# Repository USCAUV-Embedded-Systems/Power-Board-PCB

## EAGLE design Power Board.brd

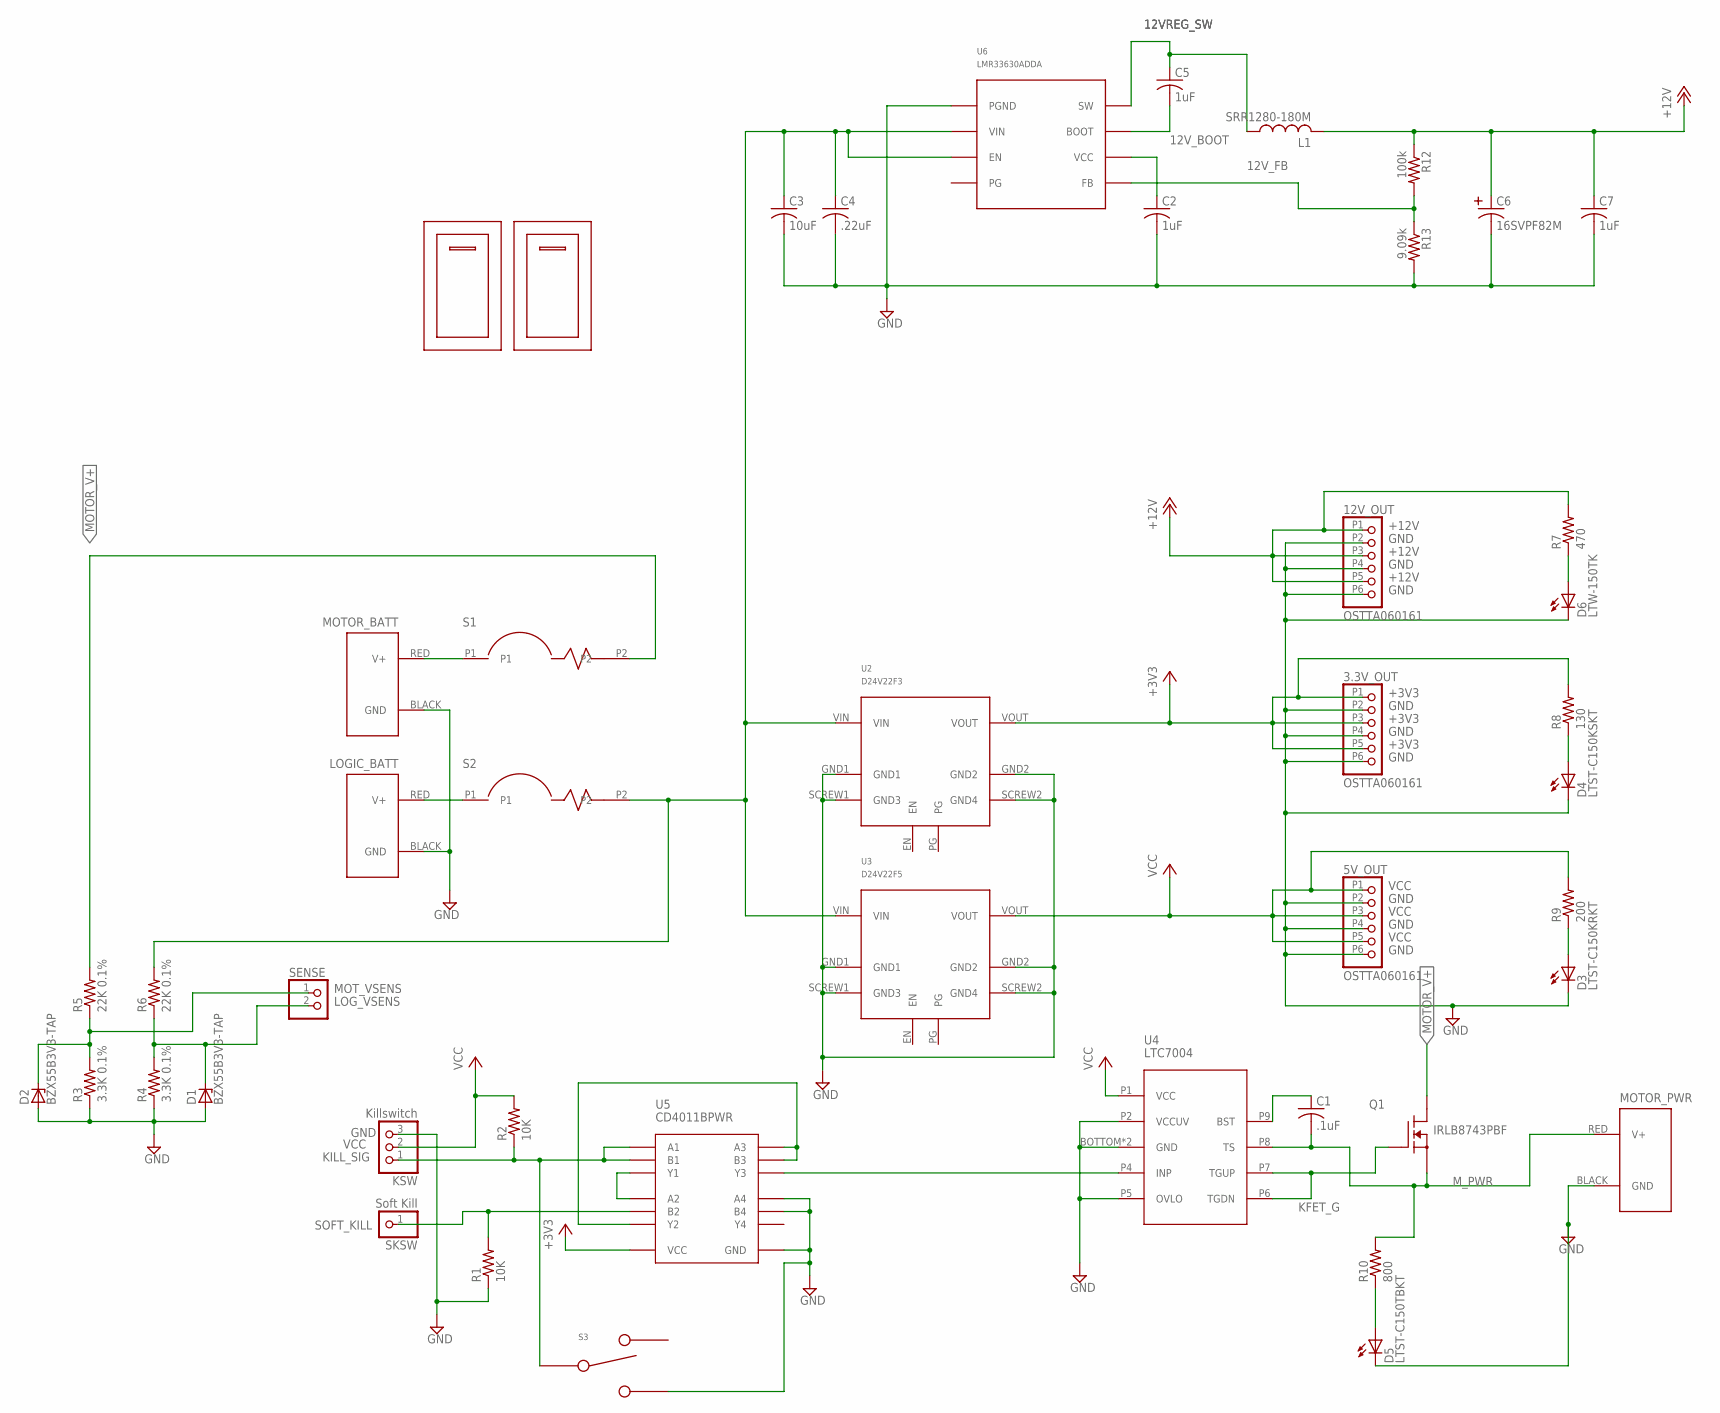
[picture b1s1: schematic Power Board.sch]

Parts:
3.3V_OUT, 5V_OUT, 12V_OUT: OSTTA060161; OSTTA06
C1: .1uF; C1206
C2, C5, C7: 1uF; C1206
C3: 10uF; C1206
C4: .22uF; C1206
C6: 16SVPF82M
D1, D2: BZX55B3V3-TAP; DO34Z7
D3: LTST-C150KRKT; LITEON_LED_1206
D4: LTST-C150KSKT; LITEON_LED_1206
D5: LTST-C150TBKT; LITEON_LED_1206
D6: LTW-150TK; LITEON_LED_1206
KSW: Killswitch; 1X03
L1: SRR1280-180M; SRR1280
LOGIC_BATT: POWERPOLE_POWER10AWG; POWERPOLE_PAIR_10AWG
MOTOR_BATT: POWERPOLE_POWER10AWG; POWERPOLE_PAIR_10AWG
MOTOR_PWR: POWERPOLE_POWER10AWG; POWERPOLE_PAIR_10AWG
Q1: IRLB8743PBF; TO220
R1, R2: 10K; R1206
R3, R4: 3.3K 0.1%; R1206
R5, R6: 22K 0.1%; R1206
R7: 470; R1206
R8: 130; R1206
R9: 200; R1206
R10: 800; R1206
R12: 100k; R1206
R13: 9.09k; R1206
S1, S2: W51-A152A1-20; W51-A152A1-PINS
S3: OS102011MS2QN1; OS102011MS2Q
SENSE: PINHD-1X2; 1X02
SKSW: Soft Kill; 1X01
U2: D24V22F3; D24V22
U3: D24V22F5; D24V22
U4: LTC7004; 10-MSOP
U5: CD4011BPWR; 14-TSSOP
U6: LMR33630ADDA; HSOIC-8-POWERPAD
U$1, U$2: W51-A152A1-20-CUTOUT; W51-A152A1-CUTOUT

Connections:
12VREG_SW: C5.1, L1.1, U6.8 (SW)
12V_BOOT: C5.2, U6.7 (BOOT)
12V_FB: R12.2, R13.1, U6.5 (FB)
+3V3: 3.3V_OUT.P1 (1), 3.3V_OUT.P3 (3), 3.3V_OUT.P5 (5), R8.2, U2.VOUT, U5.P14 (VCC)
+12V: 12V_OUT.P1 (1), 12V_OUT.P3 (3), 12V_OUT.P5 (5), C6.POS, C7.1, L1.2, R7.2, R12.1
GND: 3.3V_OUT.P2 (2), 3.3V_OUT.P4 (4), 3.3V_OUT.P6 (6), 5V_OUT.P2 (2), 5V_OUT.P4 (4), 5V_OUT.P6 (6), 12V_OUT.P2 (2), 12V_OUT.P4 (4), 12V_OUT.P6 (6), C2.2, C3.2, C4.2, C6.NEG, C7.2, D1.A, D2.A, D3.C, D4.C, D5.C, D6.C, KSW.3, LOGIC_BATT.BLACK (GND), MOTOR_BATT.BLACK (GND), MOTOR_PWR.BLACK (GND), R1.1, R3.1, R4.1, R13.2, S3.L, U2.GND1, U2.GND2, U2.SCREW1 (GND3), U2.SCREW2 (GND4), U3.GND1, U3.GND2, U3.SCREW1 (GND3), U3.SCREW2 (GND4), U4.BOTTOM (GND), U4.P2 (VCCUV), U4.P3 (GND), U4.P5 (OVLO), U5.P7 (GND), U5.P12 (A4), U5.P13 (B4), U6.1 (PGND), U6.THERMAL (PGND)
KFET_G: Q1.G, U4.P6 (TGDN), U4.P7 (TGUP)
KILL_SIG: KSW.1, R2.1, S3.C, U5.P1 (A1), U5.P2 (B1)
LOG_BATT_VIN: LOGIC_BATT.RED (V+), S2.P1
LOG_VIN: C3.1, C4.1, R6.2, S2.P2, U2.VIN, U3.VIN, U6.2 (VIN), U6.3 (EN)
LOG_VSENS: D1.C, R4.2, R6.1, SENSE.2
MOTOR_V+: Q1.D@1 (D), Q1.D@2 (D), R5.2, S1.P2
MOT_BATT_VIN: MOTOR_BATT.RED (V+), S1.P1
MOT_VSENS: D2.C, R3.2, R5.1, SENSE.1
M_PWR: C1.2, MOTOR_PWR.RED (V+), Q1.S, R10.2, U4.P8 (TS)
unnamed: D6.A, R7.1
unnamed: U5.P3 (Y1), U5.P5 (A2)
unnamed: U5.P4 (Y2), U5.P8 (A3), U5.P9 (B3)
unnamed: U4.P4 (INP), U5.P10 (Y3)
unnamed: D4.A, R8.1
unnamed: D3.A, R9.1
unnamed: D5.A, R10.1
unnamed: C2.1, U6.6 (VCC)
unnamed: C1.1, U4.P9 (BST)
SOFT_KILL: R1.2, SKSW.1, U5.P6 (B2)
VCC: 5V_OUT.P1 (1), 5V_OUT.P3 (3), 5V_OUT.P5 (5), KSW.2, R2.2, R9.2, U3.VOUT, U4.P1 (VCC)

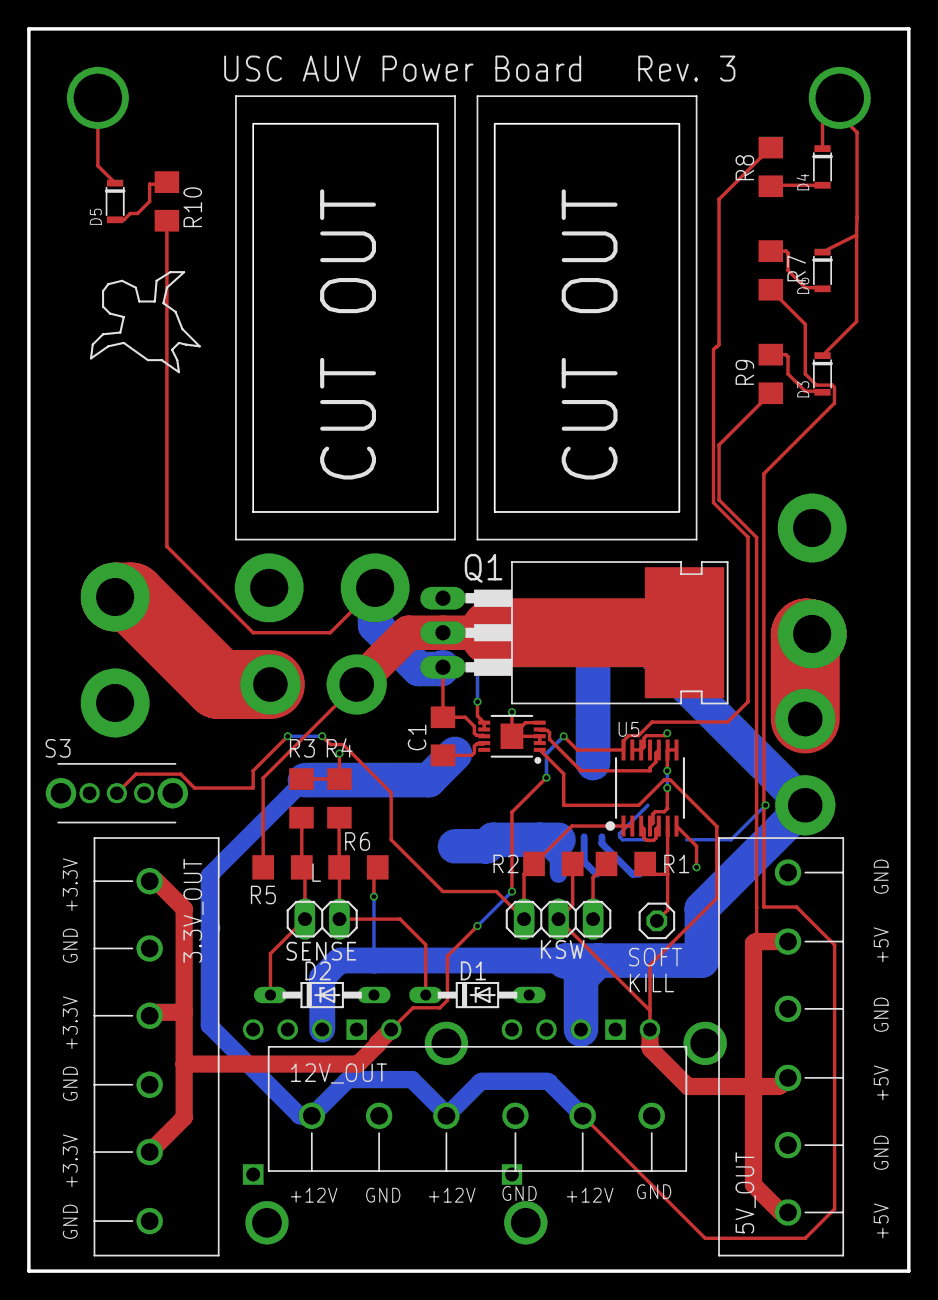
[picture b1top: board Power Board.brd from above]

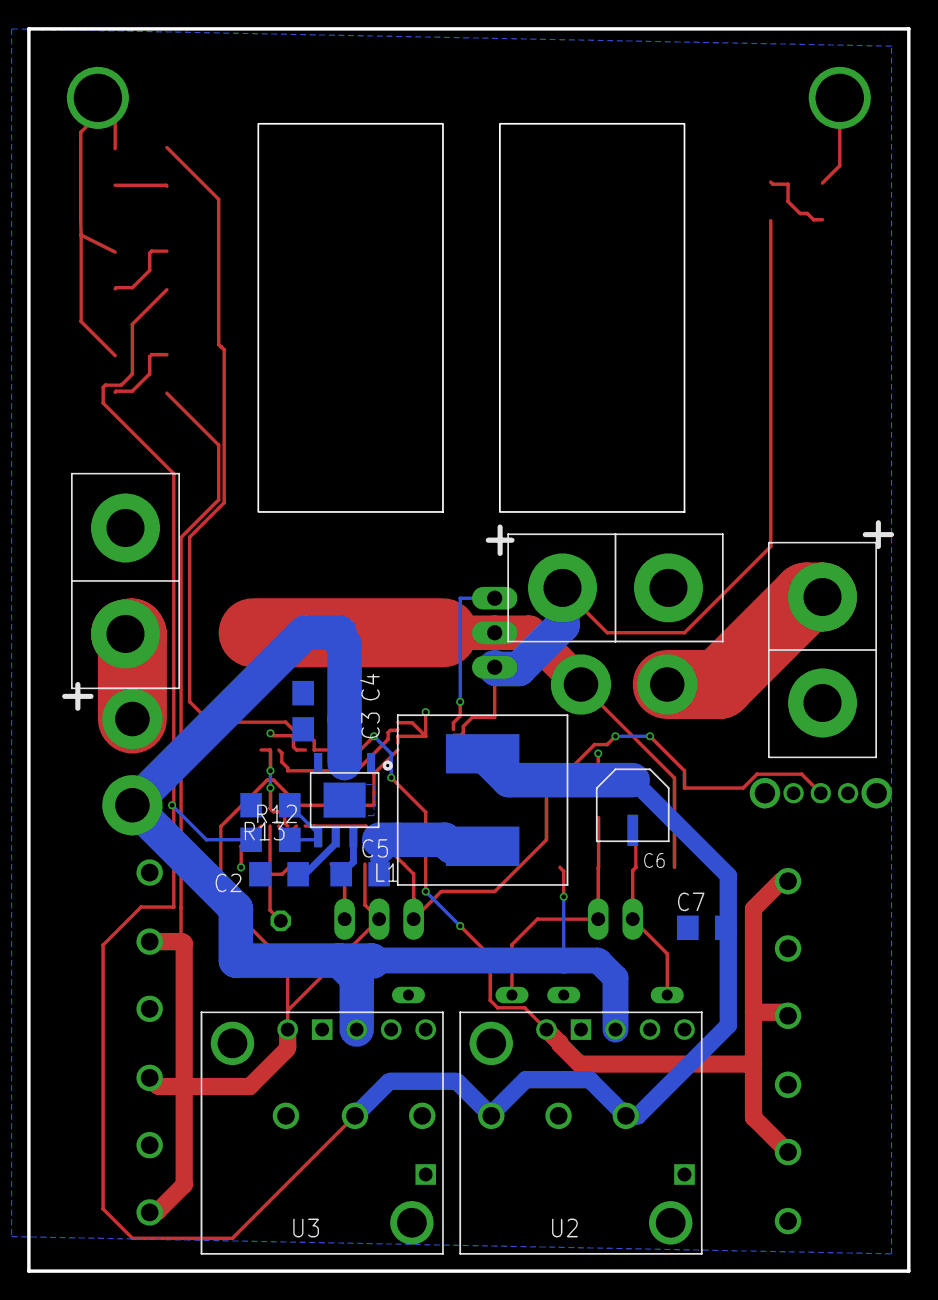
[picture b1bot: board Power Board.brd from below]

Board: 2 copper layers, 64.8 x 91.4 mm, 46 parts (15 on the bottom side), 26 nets.

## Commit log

2018-02-02 Initial commit, schematic done, need to make layout still
2018-02-02 Route PCB
2018-02-03 Add missing powerpoles.lbr
2018-02-03 Fix some routing issues for submission to PCB manufacturer
2018-04-30 Remove large LEDs (they were too hard to find, and produced too much heat)
2018-11-06 Start on new SMD version of power board -- add LTC FET driver, convert NAND gate to SMD
2018-11-20 Switch LEDs to surface mount, add LTC MOSFET driver
2019-01-09 Changes to power board
2019-01-09 Add Simple Switcher 5V regulator design (still needs to be CADed)
2019-03-06 Reroute top of board for new surface-mount parts
2019-03-06 Done with Simple Switcher-based voltage regulator
2019-03-20 Change 800 ohm resistor to 1K
